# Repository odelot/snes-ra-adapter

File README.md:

# SNES RA Adapter Project

Repository of the **SNES RetroAchievements Adapter**, a maker project that brings Internet connectivity and achievements to the original Super Nintendo, using a real console and a real cartridge, with no PC and no emulator. It is the big brother of the [NES RA Adapter](https://github.com/odelot/nes-ra-adapter), and it is powered by the amazing [RetroAchievements](https://retroachievements.org) community.

<!-- TODO: replace with the YouTube link when the video is out -->
**Video:** *coming soon*

---

## Table of Contents

- [Disclaimer](#disclaimer)
- [Introduction](#introduction)
- [Getting Started (How to Build)](#getting-started--how-to-build)
- [Architecture and Functionality](#architecture-and-functionality)
- [Compatibility](#compatibility)
- [Limitations](#limitations)
- [General Information](#general-information)
- [Version History](#version-history)
- [Roadmap](#roadmap)
- [Contributions](#contributions)
- [License](#license)
- [FAQ](#faq)
- [Acknowledgments](#acknowledgments)
- [Similar Projects](#similar-projects)

---

## Disclaimer

The project is not responsible for any use or damage it may cause. Build and use it at your own risk.

This is a **PROTOTYPE**. It works, but it still needs to evolve into a final version: revised hardware, a case, extensive testing and easy replication. v0.1 has no case, needs a small mod (2 cut traces and 2 wires), and was tested on an opened console. Only build it if you know what you're doing.

---

## Introduction

The **SNES RA Adapter** sits between the cartridge and the console, like a Game Genie. It turns your original Super Nintendo into an Internet-connected machine that unlocks RetroAchievements in real time:

- **Identifies the game** by reading the whole cartridge and computing the same MD5 hash RetroAchievements uses for ROM files. It knows exactly which game, and which version, is in the slot.
- **Monitors the console memory:** it listens to every write to the 128 KB of WRAM (DMA included) and to the cartridge save RAM, and runs rcheevos, the same code emulators use, 60 times per second.
- **Shows your progress:** on its own 1.3" screen, with a buzzer, and on a web page you can open on your phone (`http://snes-ra-adapter.local`). No app needed.

### Repository Organization

- **[hardware](hardware)**: KiCad project and Gerber files of prototype v0.1, the bill of materials, the required mod and the assembly guide.
- **[snes-pico-firmware](snes-pico-firmware)**: firmware for the WeAct Studio RP2350B Core Board. It handles cartridge identification, bus capture and rcheevos.
- **[snes-esp-firmware](snes-esp-firmware)**: firmware for the ESP32-C3 Super Mini. It handles Wi-Fi, the RetroAchievements API, the LCD, the buzzer and the web portal.
- **[misc](misc)**: auxiliary files: the `TFT_eSPI` configuration for the LCD.

---

## Getting Started / How to Build

### 1. Acquire the parts

All parts are through-hole: a 74HC4066 bus switch bank, a WeAct RP2350B board, an ESP32-C3 Super Mini, a 1.3" ST7789 LCD, a SNES 62-pin cartridge slot and a few passives. The full list is in the **[hardware bill of materials](hardware/README.md#bill-of-materials)**.

### 2. Order the PCB

Upload [`hardware/proto-v0.1/fab/snes-ra-proto-v0.1.zip`](hardware/proto-v0.1/fab/snes-ra-proto-v0.1.zip) to a pcb fab:

- 2 layers, **1.2 mm** thick (like an original cartridge).
- ENIG finish.
- Gold fingers with a 45° bevel.

### 3. Do the mod and assemble the board

Prototype v0.1 has A22 and /RD swapped on the Pico. **Every board needs 2 cut traces and 2 wires**, which are easier before the WeAct is soldered. The step by step, with pictures, and the assembly order are in the **[hardware README](hardware/README.md#required-mod-2-cuts--2-wires)**.

### 4. Flash the firmware

Flash both modules over USB **before** plugging the board into the console.

1. **Raspberry Pi Pico (WeAct RP2350B):**
   - Hold the **BOOT** button and connect the board over USB.
   - Copy `snes-pico-firmware.uf2` to the `RP2350` drive that shows up.
   - To build the `.uf2` yourself, see [snes-pico-firmware](snes-pico-firmware/README.md#building).
2. **ESP32-C3 Super Mini:**
   - Compile and upload with the Arduino IDE.
   - Then upload the `data` folder (web portal) to LittleFS.
   - Before compiling, copy [`misc/TFT_eSPI/User_Setup.h`](misc/TFT_eSPI/User_Setup.h) into your `TFT_eSPI` library folder.
   - The step by step is in [snes-esp-firmware](snes-esp-firmware/README.md).

### 5. First use

1. With the console **off**, plug the adapter into the cartridge slot and the game into the adapter.
2. Turn the console on. On the first boot, the screen asks you to configure the adapter:
   - With your phone, connect to the Wi-Fi network **`SNES_RA_ADAPTER`** (password `12345678`).
   - Open `http://192.168.1.1`.
   - Enter your Wi-Fi network and your RetroAchievements username and password.
3. The adapter connects, logs in, reads the cartridge and starts the game. Have fun!
4. To follow your progress on the phone, open `http://snes-ra-adapter.local` (the phone must be on the same Wi-Fi network).

To erase the configuration, hold the button (SW1) for 5 seconds while the adapter starts.

---

## Architecture and Functionality

```mermaid
flowchart LR
    SNES[SNES console] <-- cartridge bus --> SW[74HC4066 bus switches]
    SW <--> CART[Game cartridge]
    SW -. listen .-> PICO[RP2350B<br/>cart ID + bus capture + rcheevos]
    PICO <-- UART --> ESP[ESP32-C3<br/>Wi-Fi + LCD + buzzer + web portal]
    ESP <-- HTTPS --> RA[(RetroAchievements)]
```

### Raspberry Pi Pico (WeAct RP2350B, 48 GPIO)

- **Game identification:**
  - At power-on it holds the console in reset and isolates it from the cartridge with the bus switches.
  - It reads the whole ROM and computes its MD5. It also handles ROMs whose size is not a power of two, which show up mirrored on the bus.
  - Then it releases the console.
- **Memory monitoring (core 1):**
  - PIO state machines capture **one sample per write cycle** on the bus: WRAM writes, cartridge SRAM writes and the B-bus WRAM port ($2180–$2183), which games use to DMA data into WRAM.
  - The two PIOs of the RP2350B share an overlapping GPIO window, so no pin is duplicated.
  - Core 1 keeps a full copy of the 128 KB WRAM and of the cartridge SRAM.
- **Achievements (core 0):**
  - rcheevos runs on every **real vblank**, detected from the OAM DMA burst the game fires in the NMI handler, with a timer as fallback.
  - Each frame is evaluated on an atomic snapshot of the memory.
  - Pressing RESET on the console resets the rcheevos runtime state, just like an emulator.

More details in [snes-pico-firmware](snes-pico-firmware/README.md).

### ESP32

- **Connectivity and interface:** gives the SNES Internet access, talks to the RetroAchievements API, and shows the achievements on the LCD with sound effects on the buzzer.
- **Configuration:** Wi-Fi and RetroAchievements credentials are stored in EEPROM and set from a smartphone, through the ESP32 access point.
- **Web portal:** a dashboard on your local network (`http://snes-ra-adapter.local`). It shows:
  - the game, rich presence and progress;
  - the full achievement list with filters;
  - live unlock, challenge and progress notifications;
  - an LCD theme picker.

  The Pico is the single source of truth: the ESP32 only relays the data.

---

## Limitations

- **SA-1 games:** the SA-1 is a second processor inside the cartridge, about three times faster than the SNES CPU. It runs the game from its own memory, and most of that data never reaches the cartridge connector, so the adapter can't see it. This is a hardware limit.
- **Large cartridge save RAM:** only LoROM SRAM up to 32 KB and HiROM SRAM up to 8 KB are tracked. Achievements that read the save RAM of carts with more SRAM (Star Ocean, Tales of Phantasia, Dragon Quest VI) won't work yet. Achievements based on the console RAM are not affected.
- **Casual mode:** the prototype runs in casual mode.
- **Flash carts** (SD2SNES / FXPAK, EverDrive): not supported. The adapter needs to read the cartridge to identify the game, and with a flash cart it reads the flash cart's menu instead. To use RetroAchievements with an FXPAK, see [RA2Snes](#similar-projects).
- **Console shell:** v0.1 is a bare board, tested on an opened console. A case and a board that fits a SNES with its shell are on the [roadmap](#roadmap).
- **PAL consoles:** the firmware supports 50 Hz, but it has not been tested on a PAL console yet.

---

## General Information

- **Power:** the adapter is powered by the console's +5 V (cartridge connector). A Schottky diode keeps the USB of the modules from powering the console.
- **Logic level conversion (5 V vs 3.3 V):** there is no level shifter.
  - The RP2350 inputs are 5 V tolerant, so the Pico listens to the bus directly.
  - The Pico only drives the cartridge (at 3.3 V, which the ROMs read as HIGH) during identification, while the console is isolated by the bus switches and held in reset.

---

## Version History

- **Prototype v0.1 (2026-11):** first PCB. Everything is through-hole, with a 74HC4066 bus switch bank. Adds automatic cartridge identification (ROM MD5), cartridge SRAM capture, the B-bus WRAM port, vblank-paced frames, console reset detection and a web portal with LCD themes.

- **"Spaghetti edition" (2026-06):** WeAct RP2350B (48 GPIO) with almost 50 wires soldered straight to the console motherboard. It validated the whole bus capture by beating Star Fox, Mega Man X and EarthBound. The game was still picked from a list.
- **Proof of concept (2025-04):** reused the NES adapter with the original Pico. It could not see the whole memory range or identify games, but it caught memory writes and unlocked a few achievements.

---

## Roadmap

- **v0.1b:**
  - A22 and /RD fixed in copper (no mod).
  - ESP32-S3-Zero, for more RAM for large achievement sets.
  - A 3D-printed case in the style of the Super Game Boy, so it fits a SNES with its shell.
- **Slim version:** SN74CBT3245 bus switches, 4-layer board, about the size of a cartridge.
- **Firmware:** large SRAM carts (A17–A23 capture), ExHiROM, hardcore mode and leaderboards.

---

## Contributions

Everyone is welcome to contribute!

- Submit improvements and pull requests via GitHub.
- Join our Discord channel: [https://discord.com/invite/6eYGq7NNfF](https://discord.com/invite/6eYGq7NNfF)
- Support us on [Patreon](https://www.patreon.com/RetroAchievementsHardwareLab) or by [buying a coffee](https://buymeacoffee.com/nes.ra.adapter).

---

## License

- The source code is distributed under the **GPLv3** license.
- The PCB design files are distributed under the **CC-BY-4.0** license.

---

## FAQ

- **Q: Are you planning to sell the adapter?**
- **A:** No. This is a fully open-source, community-driven DIY project.
<br/>

- **Q: So how can I get one?**
- **A:** It's a DIY project: you can build it yourself! Every part is through-hole, so it is a good soldering project. As with other open-source projects, the community may step in to build units for people who don't want to build their own.
<br/>

- **Q: Do I need to modify my SNES?**
- **A:** No. The adapter plugs into the cartridge slot. The prototype v0.1 is a bare board, though, and was tested on an opened console. The next revision fits a SNES with its shell.
<br/>

- **Q: Do I need to connect it to a computer?**
- **A:** No! It has built-in Wi-Fi and all achievement processing happens on the adapter. You configure it from your phone.
<br/>

- **Q: Will it work with Super Famicom?**
- **A:** The cartridge connector is the same, but it has not been tested yet.
<br/>

- **Q: Why doesn't Super Mario RPG work?**
- **A:** It uses the SA-1 chip, which keeps the game data inside the cartridge, where the adapter can't see it. See [Limitations](#limitations).
<br/>

---

## Acknowledgments

- Thanks to **RetroAchievements** and its community for providing achievements for nearly all games, and for always supporting, testing and sharing.
- Thanks to the **Patreon supporters**, who covered part of the cost of these prototypes.

## Similar Projects

- **RA2Snes**: [https://github.com/Factor-64/RA2Snes](https://github.com/Factor-64/RA2Snes). A program built with Qt and C++ that bridges the QUsb2Snes web server and the rcheevos client, so you can unlock achievements on real Super Nintendo hardware through the SD2Snes USB port.
- **NES RA Adapter**: [https://github.com/odelot/nes-ra-adapter](https://github.com/odelot/nes-ra-adapter). The same idea for the NES and the Famicom.

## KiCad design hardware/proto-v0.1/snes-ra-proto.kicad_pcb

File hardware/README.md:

# SNES RA Adapter: hardware

The adapter is a single board that works like a Game Genie. Its bottom edge plugs into the console's cartridge slot, and the game cartridge plugs into a female slot on its top edge. The screen sits on the front.

```
hardware/
  proto-v0.1/        KiCad 9 project of prototype v0.1, exactly as fabricated and tested
    fab/             Gerber + drill zip, ready to upload to a pcb fab
  lib/               custom symbols and footprints used by the project (snes-ra-adapter)
  docs/
    netlist.md       full connection table (edge pin -> switch -> Pico GPIO, ESP32, power)
    v0.1-mod/        images of the 2 cuts + 2 wires every v0.1 board needs
```

---

## Prototype v0.1

- **Board:** 120 × 110 mm, 2 layers, 1.2 mm thick (the same as an original cartridge). Every part is through-hole, so it is beginner-friendly to solder.
- **Bus isolation:** 9× 74HC4066 (DIP-14) on 35 lines: A0–A23, D0–D7, /RD, /WR and /CART. While the adapter reads the cartridge, the switches open and the console is held in reset. During gameplay they stay closed and the Pico only listens.
- **Microcontrollers:** WeAct Studio RP2350B Core Board (48 GPIO) and ESP32-C3 Super Mini, both soldered as modules.
- **Screen:** 1.3" 240×240 ST7789 LCD (7-pin) in a 1x7 female header.
- **Bottom strip (30 mm):** this is the part that goes into the console. It is 89 mm wide and has no components.
- **Pico USB-C:** points down, through a corridor with no components, so the cable still fits with the board in the console.
- **Back face:**
  - The ESP32-C3 sits behind the LCD, with its USB on the left edge. There is no copper plane under its antenna.
  - The buzzer (BZ1), its driver transistor (Q2) and R4 are next to it.
- **Tested on an opened console.** v0.1 has no case and was not designed around the SNES shell or the power-switch lock. The case and the shell fit come in the next revision (v0.1b).

The complete connection table is in [docs/netlist.md](docs/netlist.md).

### Bill of materials

| Qty | Part | Refs |
|---:|---|---|
| 1 | PCB (see [Ordering the PCB](#ordering-the-pcb)) | |
| 1 | SNES 62-pin cartridge slot, 2.5 mm pitch | J2 |
| 9 | 74HC4066 DIP-14 (sockets optional) | U1–U9 |
| 1 | WeAct Studio RP2350B Core Board + 2× female headers | U10 |
| 1 | ESP32-C3 Super Mini (the PLUS version with an external antenna works better) + female headers | U11 |
| 1 | LCD 1.3" 240×240 ST7789, 7 pins + 1x7 female header | J3 |
| 9 | 100 nF ceramic capacitor (5 mm pitch) | C1–C9 |
| 1 | 47 µF 16 V electrolytic capacitor | C10 |
| 1 | 10 µF 10 V (or higher) electrolytic capacitor | C11 |
| 1 | 1N5817 Schottky diode | D1 |
| 2 | BC548 NPN transistor | Q1, Q2 |
| 3 | 10 kΩ resistor | R1, R3, R5 |
| 2 | 1 kΩ resistor | R2, R4 |
| 1 | Passive buzzer, 12 mm | BZ1 |
| 1 | 6×6 mm tactile push button | SW1 |
| 1 | Bi-color LED 3 mm, green/red, common cathode (*optional*) | D2 |
| 2 | 100 Ω resistor (*optional*, only with D2) | R6, R7 |
| 1 | 1x3 pin header (*optional*, UART debug) | J4 |
| 2 | Short pieces of thin insulated wire (for the [mod](#required-mod-2-cuts--2-wires)) | |

Notes:

- **Resistors:** mounted standing up (2.54 mm pitch).
- **JP1:** a solder jumper that comes bridged 1-2 from the factory (pull-down, so the bus starts isolated at power-on). Leave it as is.
- **BZ1:** the footprint has 5.0 mm between the legs (TDK PS1240). The common 12 mm passive buzzers have 6.5 mm, so bend the legs inwards to fit.
- **C10 and C11:** the footprints are for Ø6.3 mm / 2.5 mm and Ø5 mm / 2.0 mm parts. Smaller capacitors (Ø4 mm, 1.5 mm pitch) also fit, just open the legs a little.
- **J4:** an optional UART debug header (1 GND, 2 Pico TX, 3 Pico RX).

### Ordering the PCB

Upload [`proto-v0.1/fab/snes-ra-proto-v0.1.zip`](proto-v0.1/fab/snes-ra-proto-v0.1.zip) to a pcb fab. These are the settings used for the tested boards:

- 2 layers, **1.2 mm** thick.
- ENIG surface finish.
- **Gold fingers: yes**, with a **45° bevel** on the edge connector.

### Required mod (2 cuts + 2 wires)

Prototype v0.1 has two Pico pins swapped. A22 goes to GP37 and /RD goes to GP29, but the firmware needs **A22 on GP29**. That is because GP29 is inside the PIO0 capture window, and A22 tells a WRAM mirror access from a direct $7E/$7F access. **Every v0.1 board needs this mod.** It is already fixed in copper in the next revision.

The marks below are on the WeAct (U10) footprint, on the PCB itself. The cuts are easiest **before** soldering the WeAct headers. Use a hobby knife, and scrape until the copper is gone.

1. **Cut 1 (front, screen side):** cut the trace that leaves the **GP29** pad, right next to the pad.

2. **Cut 2 (back, solder side):** cut the trace that leaves the **GP37** pad, right next to the pad.
3. **Wire 1:** solder a wire from **GP29** to **U6 pin 3** (A22).
4. **Wire 2:** solder a wire from **GP37** to **U9 pin 3** (/RD).

5. **Check with a multimeter:**
   - GP29 must have continuity with U6 pin 3, and **not** with U9 pin 3.
   - GP37 must have continuity with U9 pin 3, and **not** with U6 pin 3.

The Pico firmware expects the mod by default (`#define A22_ON_GP29` in `snes-pico-firmware/src/main.c`).

### Assembly order

1. **Mod:** make the [2 cuts](#required-mod-2-cuts--2-wires).
2. **Low parts first:** resistors, diode, ceramic capacitors and the 74HC4066 (or their sockets). Watch the orientation of U1–U9.
3. **Back parts:** ESP32-C3 headers, BZ1, Q2 and R4. Their pins come out on the front, under the LCD, so solder them **before** the LCD header.
4. **Front parts:** Q1, electrolytic capacitors, SW1, the optional D2 and the WeAct headers.
5. **LCD header and cartridge slot (J2).**
6. **Mod wires:** solder the 2 wires on the back.
7. **Before the first power-up:**
   - Check that there is no short between +5V and GND.
   - Flash both firmwares over USB, **with the board out of the console**.
   - Then plug the modules in.

### Status

- **v0.1:** fabricated (Oct 2026) and tested with the mod above.
- **Games beaten / tested:** Super Mario World, Super Metroid, Star Fox and Yoshi's Island (see the main [README](../README.md)).
- **KiCad files:** ERC has 0 violations. DRC shows 0 violations, 0 unconnected items and 0 schematic parity issues. The files are the ones that went to fab, so they still have the swap the mod fixes.

---

## What's next

- **v0.1b:** v0.1 with A22 and /RD fixed in copper, ESP32-S3-Zero instead of the C3 (more RAM for large achievement sets) and parts placed for a 3D-printed case in the style of the Super Game Boy, so it fits a SNES with its shell.
- **Slim version:** SN74CBT3245 bus switches instead of the 4066s, 4 layers, about the size of a cartridge board.

These boards are still being validated and will be published once they are tested.

## License

The PCB design files are distributed under the **CC-BY-4.0** license.

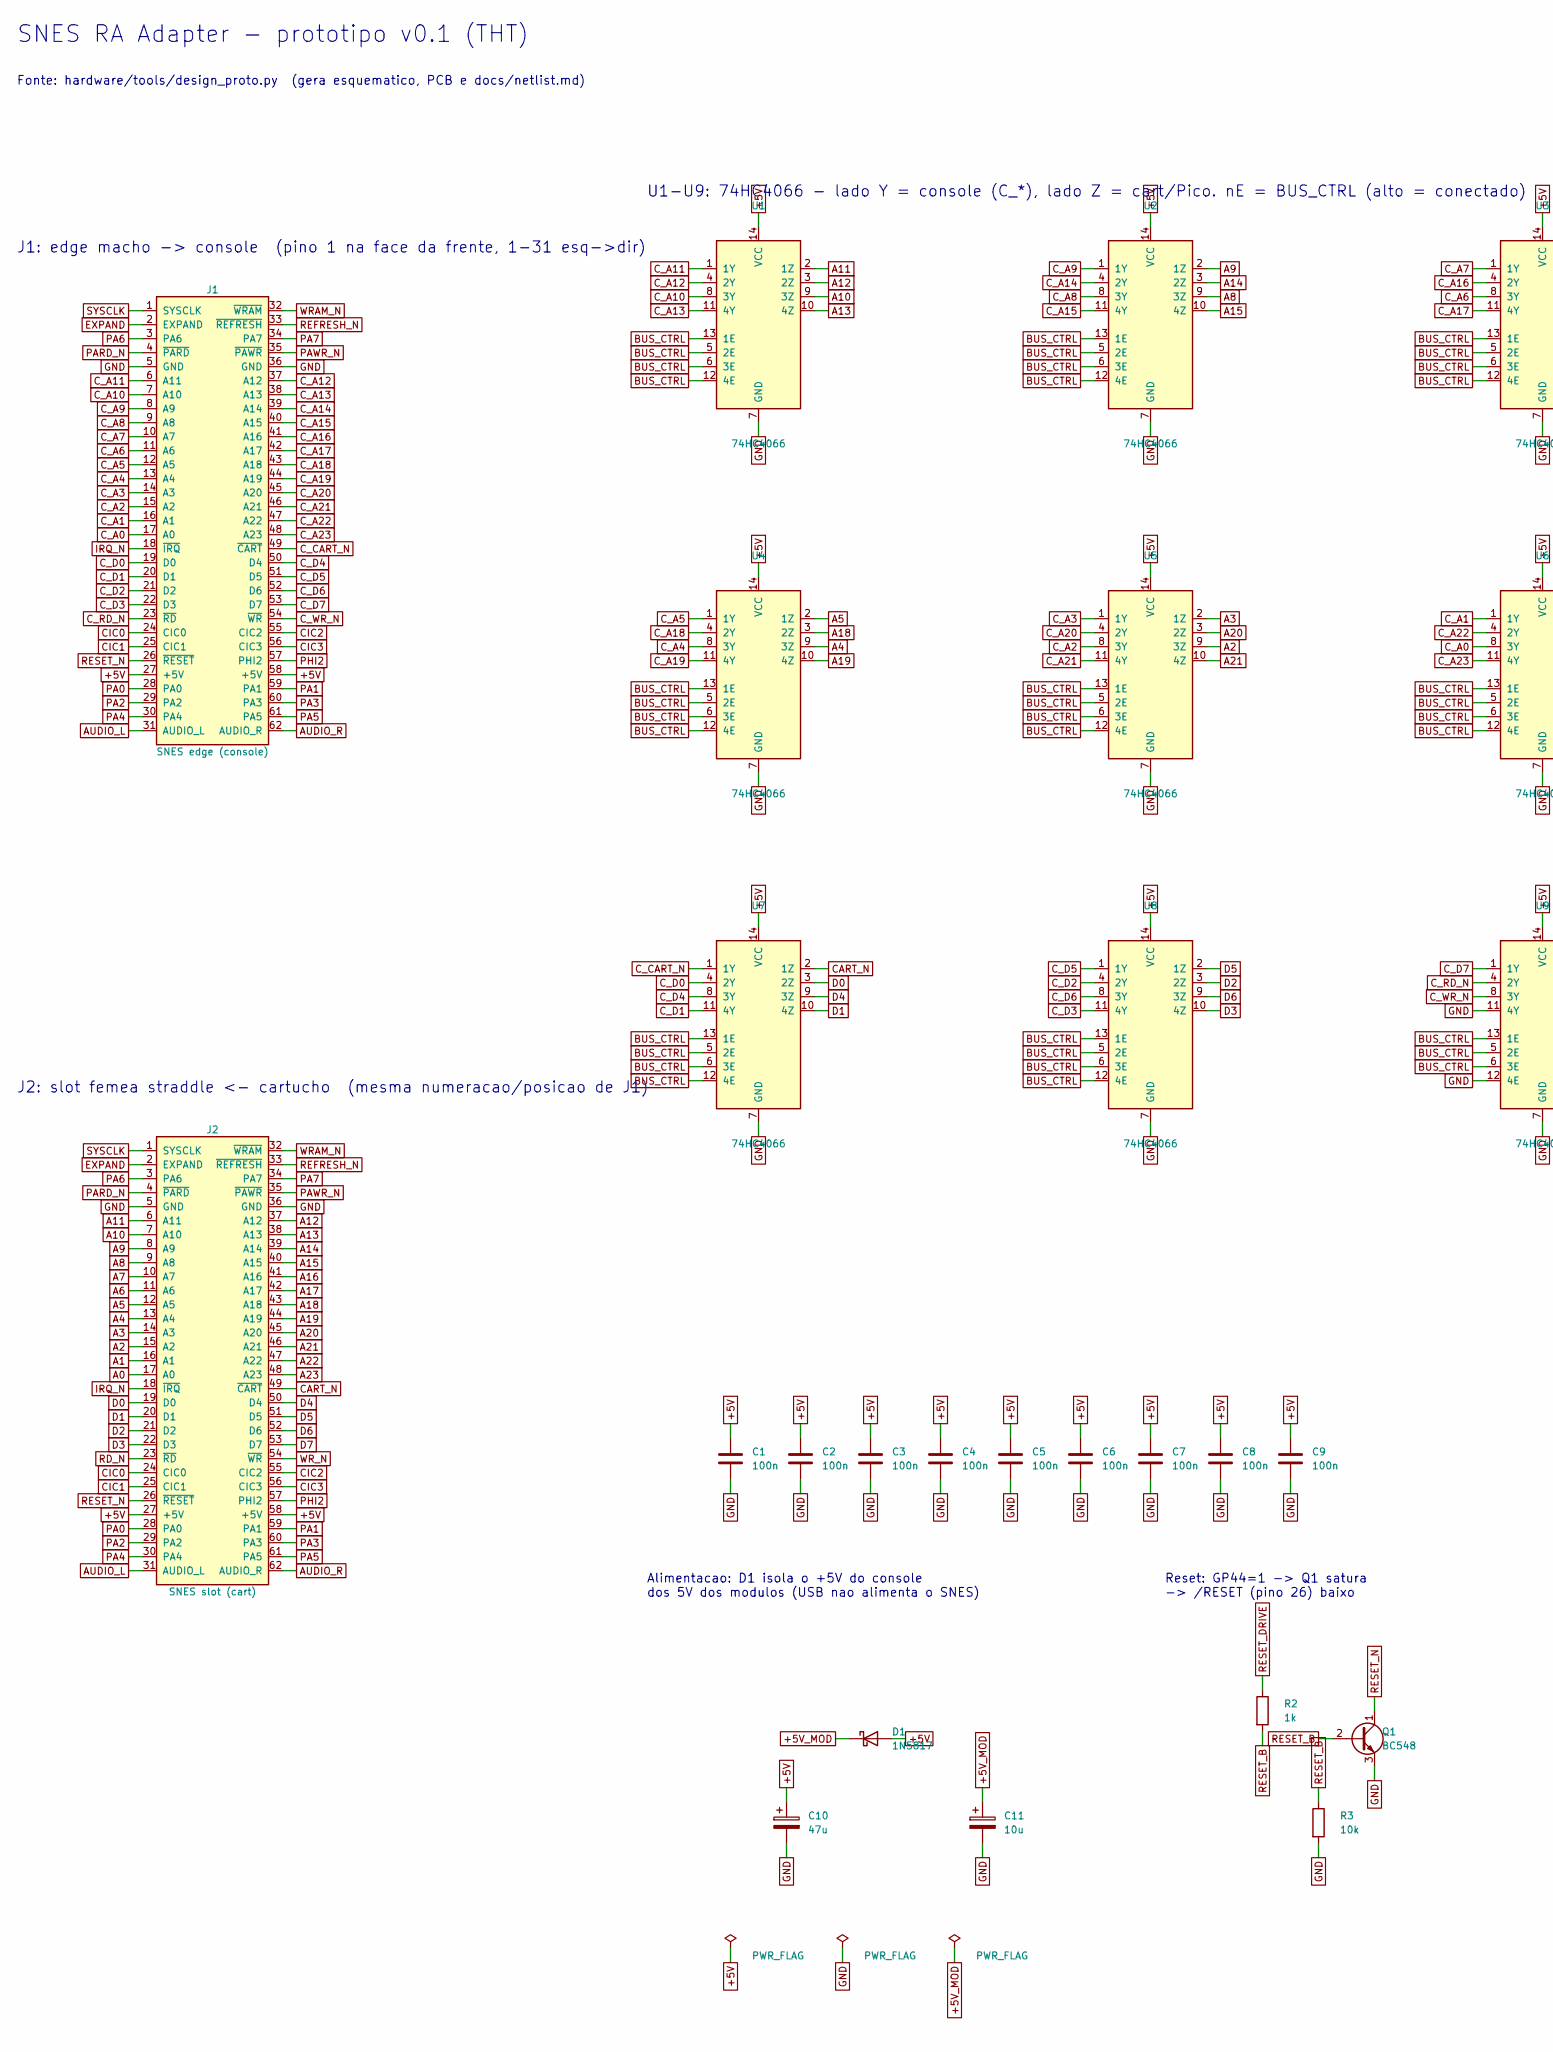
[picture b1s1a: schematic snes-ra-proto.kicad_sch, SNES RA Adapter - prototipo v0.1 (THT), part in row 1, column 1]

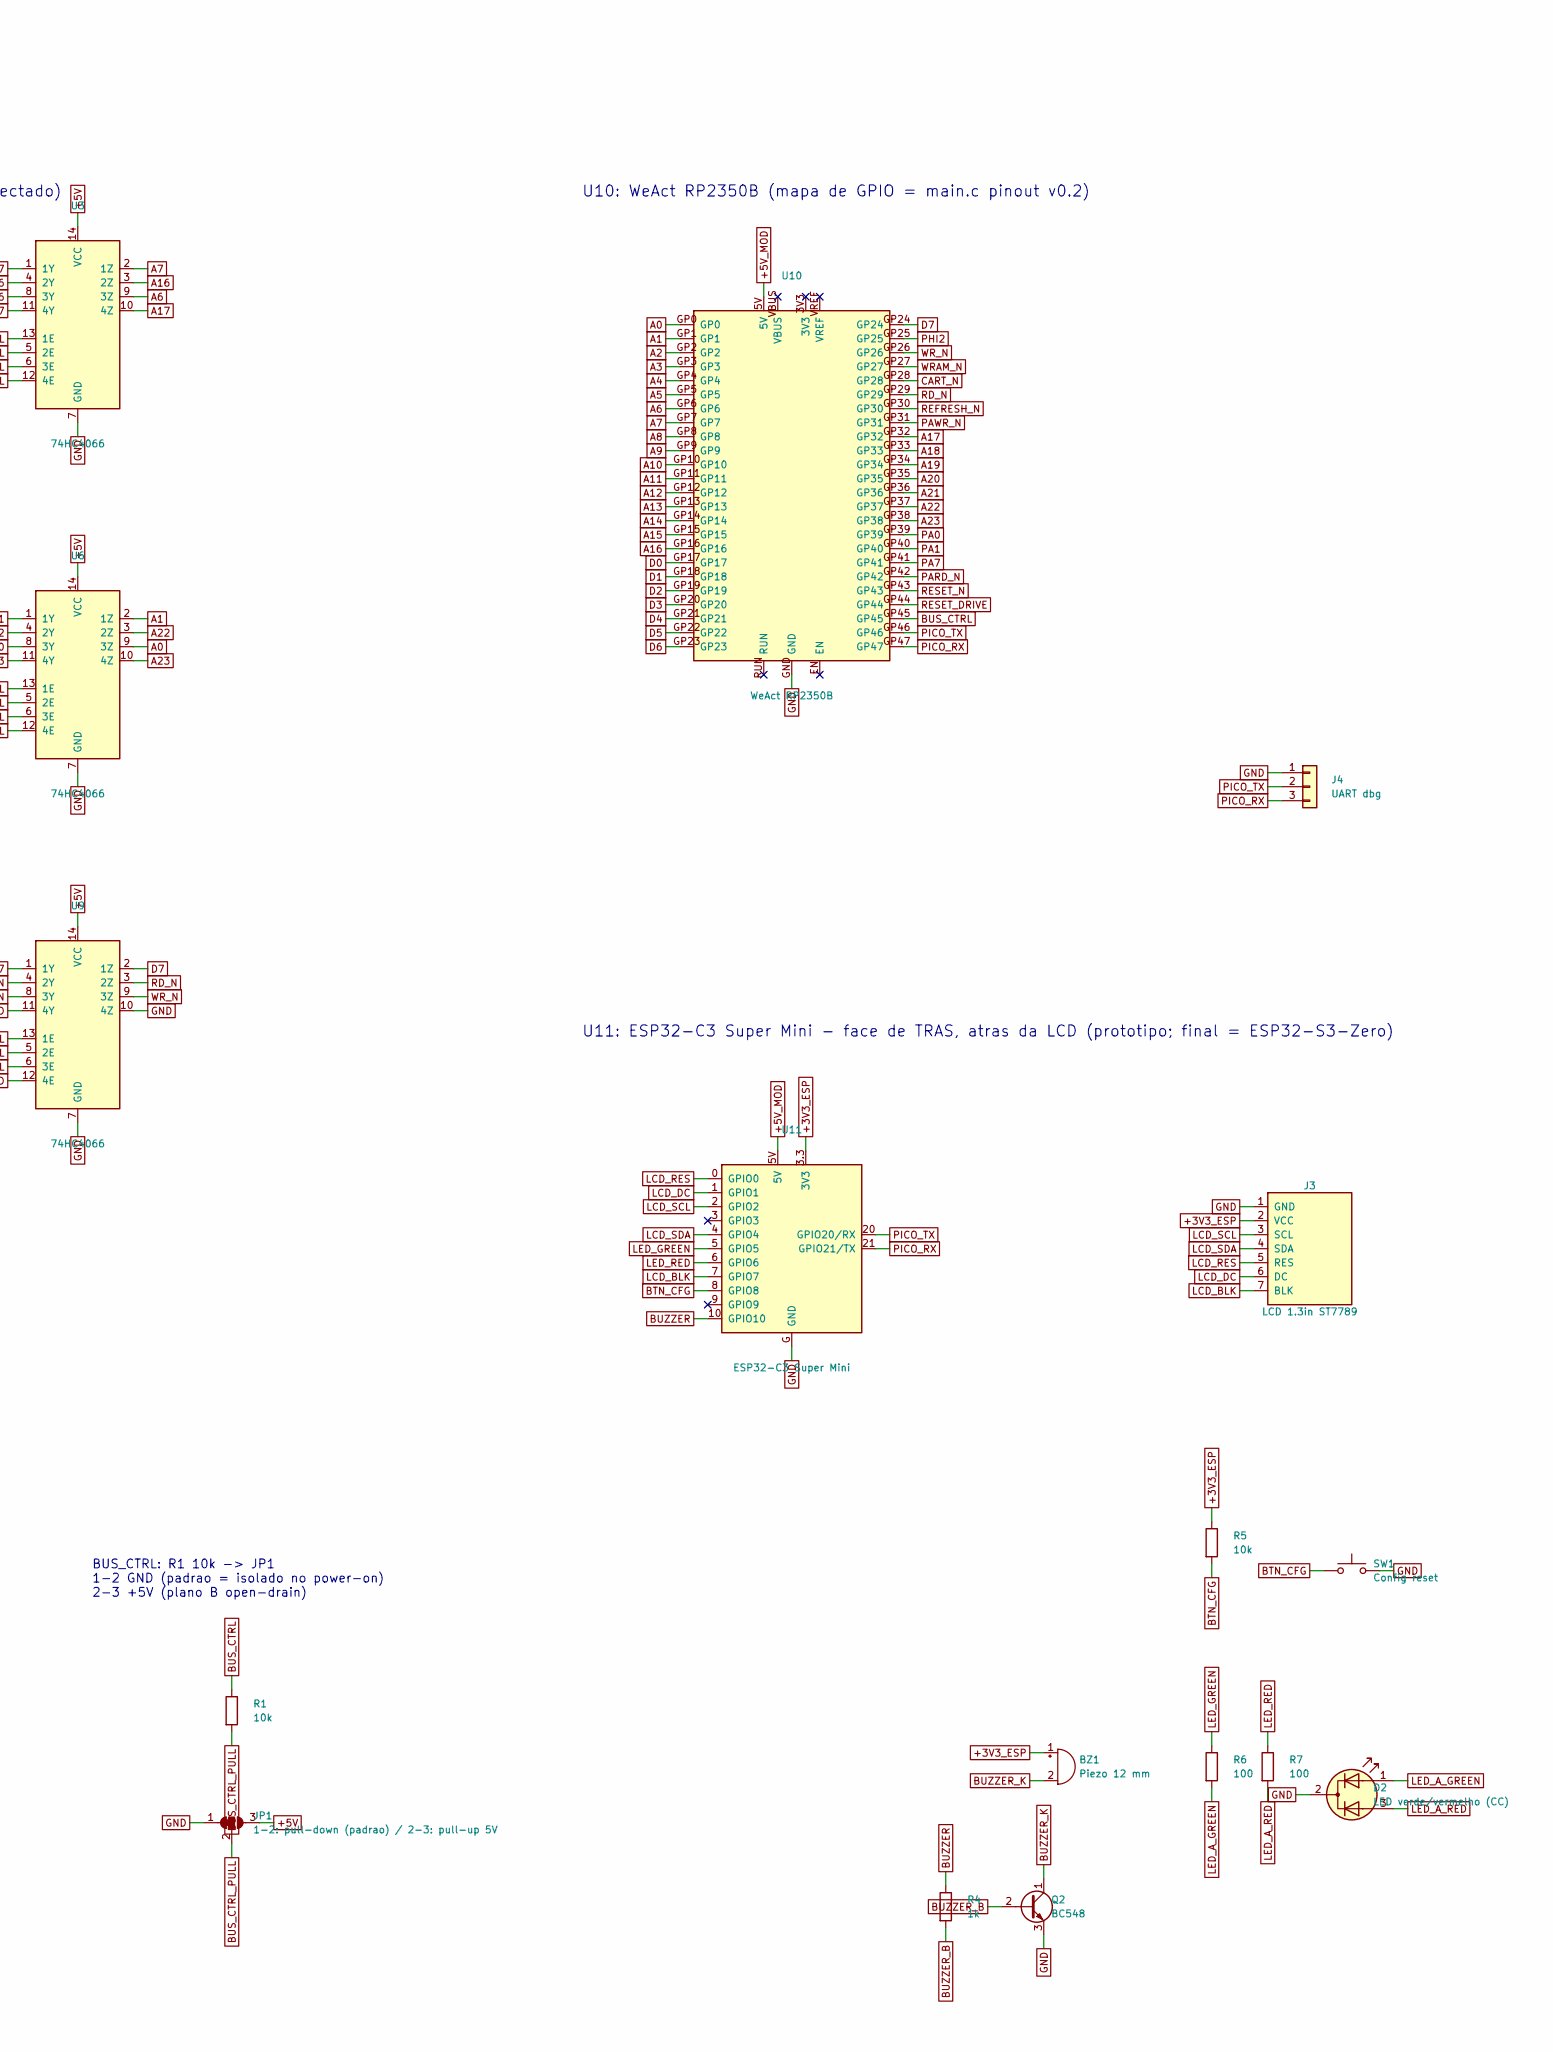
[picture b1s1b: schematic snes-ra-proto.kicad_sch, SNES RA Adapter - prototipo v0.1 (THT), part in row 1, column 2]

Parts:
BZ1: Piezo 12 mm; Buzzer_TDK_PS1240P02BT_D12.2mm_H6.5mm
C1, C2, C3, C4, C5, C6, C7, C8, C9: 100n; C_Disc_D5.0mm_W2.5mm_P5.00mm
C10: 47u; CP_Radial_D6.3mm_P2.50mm
C11: 10u; CP_Radial_D5.0mm_P2.00mm
D1: 1N5817; D_DO-41_SOD81_P10.16mm_Horizontal
D2: LED verde/vermelho (CC); LED_D3.0mm-3
J1: SNES edge (console); SNES_CartEdge_62
J2: SNES slot (cart); SNES_Slot_62_Straddle
J3: LCD 1.3in ST7789; LCD_ST7789_1.3in_7pin
J4: UART dbg; PinHeader_1x03_P2.54mm_Vertical
JP1: 1-2: pull-down (padrao) / 2-3: pull-up 5V; SolderJumper-3_P1.3mm_Bridged12_RoundedPad1.0x1.5mm
Q1, Q2: BC548; TO-92_Inline
R1, R3, R5: 10k; R_Axial_DIN0207_L6.3mm_D2.5mm_P2.54mm_Vertical
R2, R4: 1k; R_Axial_DIN0207_L6.3mm_D2.5mm_P2.54mm_Vertical
R6, R7: 100; R_Axial_DIN0207_L6.3mm_D2.5mm_P2.54mm_Vertical
SW1: Config reset; SW_PUSH_6mm
U1, U2, U3, U4, U5, U6, U7, U8, U9: 74HC4066; DIP-14_W7.62mm
U10: WeAct RP2350B; WeAct_RP2350B_CoreBoard
U11: ESP32-C3 Super Mini; ESP32-C3_SuperMini

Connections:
+3V3_ESP: BZ1.1 (+), J3.2 (VCC), R5.1, U11.3.3 (3V3)
+5V: C1.1, C2.1, C3.1, C4.1, C5.1, C6.1, C7.1, C8.1, C9.1, C10.1, D1.2 (A), J1.27 (+5V), J1.58 (+5V), J2.27 (+5V), J2.58 (+5V), JP1.3 (B), U1.14 (VCC), U2.14 (VCC), U3.14 (VCC), U4.14 (VCC), U5.14 (VCC), U6.14 (VCC), U7.14 (VCC), U8.14 (VCC), U9.14 (VCC)
+5V_MOD: C11.1, D1.1 (K), U10.5V, U11.5V
A0: J2.17 (A0), U6.9 (3Z), U10.GP0
A1: J2.16 (A1), U6.2 (1Z), U10.GP1
A2: J2.15 (A2), U5.9 (3Z), U10.GP2
A3: J2.14 (A3), U5.2 (1Z), U10.GP3
A4: J2.13 (A4), U4.9 (3Z), U10.GP4
A5: J2.12 (A5), U4.2 (1Z), U10.GP5
A6: J2.11 (A6), U3.9 (3Z), U10.GP6
A7: J2.10 (A7), U3.2 (1Z), U10.GP7
A8: J2.9 (A8), U2.9 (3Z), U10.GP8
A9: J2.8 (A9), U2.2 (1Z), U10.GP9
A10: J2.7 (A10), U1.9 (3Z), U10.GP10
A11: J2.6 (A11), U1.2 (1Z), U10.GP11
A12: J2.37 (A12), U1.3 (2Z), U10.GP12
A13: J2.38 (A13), U1.10 (4Z), U10.GP13
A14: J2.39 (A14), U2.3 (2Z), U10.GP14
A15: J2.40 (A15), U2.10 (4Z), U10.GP15
A16: J2.41 (A16), U3.3 (2Z), U10.GP16
A17: J2.42 (A17), U3.10 (4Z), U10.GP32
A18: J2.43 (A18), U4.3 (2Z), U10.GP33
A19: J2.44 (A19), U4.10 (4Z), U10.GP34
A20: J2.45 (A20), U5.3 (2Z), U10.GP35
A21: J2.46 (A21), U5.10 (4Z), U10.GP36
A22: J2.47 (A22), U6.3 (2Z), U10.GP37
A23: J2.48 (A23), U6.10 (4Z), U10.GP38
AUDIO_L: J1.31 (AUDIO_L), J2.31 (AUDIO_L)
AUDIO_R: J1.62 (AUDIO_R), J2.62 (AUDIO_R)
BTN_CFG: R5.2, SW1.1, U11.8 (GPIO8)
BUS_CTRL: R1.1, U1.5 (2E), U1.6 (3E), U1.12 (4E), U1.13 (1E), U2.5 (2E), U2.6 (3E), U2.12 (4E), U2.13 (1E), U3.5 (2E), U3.6 (3E), U3.12 (4E), U3.13 (1E), U4.5 (2E), U4.6 (3E), U4.12 (4E), U4.13 (1E), U5.5 (2E), U5.6 (3E), U5.12 (4E), U5.13 (1E), U6.5 (2E), U6.6 (3E), U6.12 (4E), U6.13 (1E), U7.5 (2E), U7.6 (3E), U7.12 (4E), U7.13 (1E), U8.5 (2E), U8.6 (3E), U8.12 (4E), U8.13 (1E), U9.5 (2E), U9.6 (3E), U9.13 (1E), U10.GP45
BUS_CTRL_PULL: JP1.2 (C), R1.2
BUZZER: R4.1, U11.10 (GPIO10)
BUZZER_B: Q2.2 (B), R4.2
BUZZER_K: BZ1.2 (-), Q2.1 (C)
CART_N: J2.49 (~CART), U7.2 (1Z), U10.GP28
CIC0: J1.24 (CIC0), J2.24 (CIC0)
CIC1: J1.25 (CIC1), J2.25 (CIC1)
CIC2: J1.55 (CIC2), J2.55 (CIC2)
CIC3: J1.56 (CIC3), J2.56 (CIC3)
C_A0: J1.17 (A0), U6.8 (3Y)
C_A1: J1.16 (A1), U6.1 (1Y)
C_A2: J1.15 (A2), U5.8 (3Y)
C_A3: J1.14 (A3), U5.1 (1Y)
C_A4: J1.13 (A4), U4.8 (3Y)
C_A5: J1.12 (A5), U4.1 (1Y)
C_A6: J1.11 (A6), U3.8 (3Y)
C_A7: J1.10 (A7), U3.1 (1Y)
C_A8: J1.9 (A8), U2.8 (3Y)
C_A9: J1.8 (A9), U2.1 (1Y)
C_A10: J1.7 (A10), U1.8 (3Y)
C_A11: J1.6 (A11), U1.1 (1Y)
C_A12: J1.37 (A12), U1.4 (2Y)
C_A13: J1.38 (A13), U1.11 (4Y)
C_A14: J1.39 (A14), U2.4 (2Y)
C_A15: J1.40 (A15), U2.11 (4Y)
C_A16: J1.41 (A16), U3.4 (2Y)
C_A17: J1.42 (A17), U3.11 (4Y)
C_A18: J1.43 (A18), U4.4 (2Y)
C_A19: J1.44 (A19), U4.11 (4Y)
C_A20: J1.45 (A20), U5.4 (2Y)
C_A21: J1.46 (A21), U5.11 (4Y)
C_A22: J1.47 (A22), U6.4 (2Y)
C_A23: J1.48 (A23), U6.11 (4Y)
C_CART_N: J1.49 (~CART), U7.1 (1Y)
C_D0: J1.19 (D0), U7.4 (2Y)
C_D1: J1.20 (D1), U7.11 (4Y)
C_D2: J1.21 (D2), U8.4 (2Y)
C_D3: J1.22 (D3), U8.11 (4Y)
C_D4: J1.50 (D4), U7.8 (3Y)
C_D5: J1.51 (D5), U8.1 (1Y)
C_D6: J1.52 (D6), U8.8 (3Y)
C_D7: J1.53 (D7), U9.1 (1Y)
C_RD_N: J1.23 (~RD), U9.4 (2Y)
C_WR_N: J1.54 (~WR), U9.8 (3Y)
D0: J2.19 (D0), U7.3 (2Z), U10.GP17
D1: J2.20 (D1), U7.10 (4Z), U10.GP18
D2: J2.21 (D2), U8.3 (2Z), U10.GP19
D3: J2.22 (D3), U8.10 (4Z), U10.GP20
D4: J2.50 (D4), U7.9 (3Z), U10.GP21
D5: J2.51 (D5), U8.2 (1Z), U10.GP22
D6: J2.52 (D6), U8.9 (3Z), U10.GP23
D7: J2.53 (D7), U9.2 (1Z), U10.GP24
EXPAND: J1.2 (EXPAND), J2.2 (EXPAND)
GND: C1.2, C2.2, C3.2, C4.2, C5.2, C6.2, C7.2, C8.2, C9.2, C10.2, C11.2, D2.2 (K), J1.5 (GND), J1.36 (GND), J2.5 (GND), J2.36 (GND), J3.1 (GND), J4.1, JP1.1 (A), Q1.3 (E), Q2.3 (E), R3.2, SW1.2, U1.7 (GND), U2.7 (GND), U3.7 (GND), U4.7 (GND), U5.7 (GND), U6.7 (GND), U7.7 (GND), U8.7 (GND), U9.7 (GND), U9.10 (4Z), U9.11 (4Y), U9.12 (4E), U10.GND, U11.G (GND)
IRQ_N: J1.18 (~IRQ), J2.18 (~IRQ)
LCD_BLK: J3.7 (BLK), U11.7 (GPIO7)
LCD_DC: J3.6 (DC), U11.1 (GPIO1)
LCD_RES: J3.5 (RES), U11.0 (GPIO0)
LCD_SCL: J3.3 (SCL), U11.2 (GPIO2)
LCD_SDA: J3.4 (SDA), U11.4 (GPIO4)
LED_A_GREEN: D2.1 (A1), R6.2
LED_A_RED: D2.3 (A2), R7.2
LED_GREEN: R6.1, U11.5 (GPIO5)
LED_RED: R7.1, U11.6 (GPIO6)
PA0: J1.28 (PA0), J2.28 (PA0), U10.GP39
PA1: J1.59 (PA1), J2.59 (PA1), U10.GP40
PA2: J1.29 (PA2), J2.29 (PA2)
PA3: J1.60 (PA3), J2.60 (PA3)
PA4: J1.30 (PA4), J2.30 (PA4)
PA5: J1.61 (PA5), J2.61 (PA5)
PA6: J1.3 (PA6), J2.3 (PA6)
PA7: J1.34 (PA7), J2.34 (PA7), U10.GP41
PARD_N: J1.4 (~PARD), J2.4 (~PARD), U10.GP42
PAWR_N: J1.35 (~PAWR), J2.35 (~PAWR), U10.GP31
PHI2: J1.57 (PHI2), J2.57 (PHI2), U10.GP25
PICO_RX: J4.3, U10.GP47, U11.21 (GPIO21/TX)
PICO_TX: J4.2, U10.GP46, U11.20 (GPIO20/RX)
RD_N: J2.23 (~RD), U9.3 (2Z), U10.GP29
REFRESH_N: J1.33 (~REFRESH), J2.33 (~REFRESH), U10.GP30
RESET_B: Q1.2 (B), R2.2, R3.1
RESET_DRIVE: R2.1, U10.GP44
RESET_N: J1.26 (~RESET), J2.26 (~RESET), Q1.1 (C), U10.GP43
SYSCLK: J1.1 (SYSCLK), J2.1 (SYSCLK)
WRAM_N: J1.32 (~WRAM), J2.32 (~WRAM), U10.GP27
WR_N: J2.54 (~WR), U9.9 (3Z), U10.GP26

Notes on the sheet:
SNES RA Adapter - prototipo v0.1 (THT)
Fonte: hardware/tools/design_proto.py (gera esquematico, PCB e docs/netlist.md)
J1: edge macho -> console (pino 1 na face da frente, 1-31 esq->dir)
J2: slot femea straddle <- cartucho (mesma numeracao/posicao de J1)
U1-U9: 74HC4066 - lado Y = console (C_*), lado Z = cart/Pico. nE = BUS_CTRL (alto = conectado)
Alimentacao: D1 isola o +5V do console dos 5V dos modulos (USB nao alimenta o SNES)
Reset: GP44=1 -> Q1 satura -> /RESET (pino 26) baixo
BUS_CTRL: R1 10k -> JP1 1-2 GND (padrao = isolado no power-on) 2-3 +5V (plano B open-drain)
U10: WeAct RP2350B (mapa de GPIO = main.c pinout v0.2)
U11: ESP32-C3 Super Mini - face de TRAS, atras da LCD (prototipo; final = ESP32-S3-Zero)

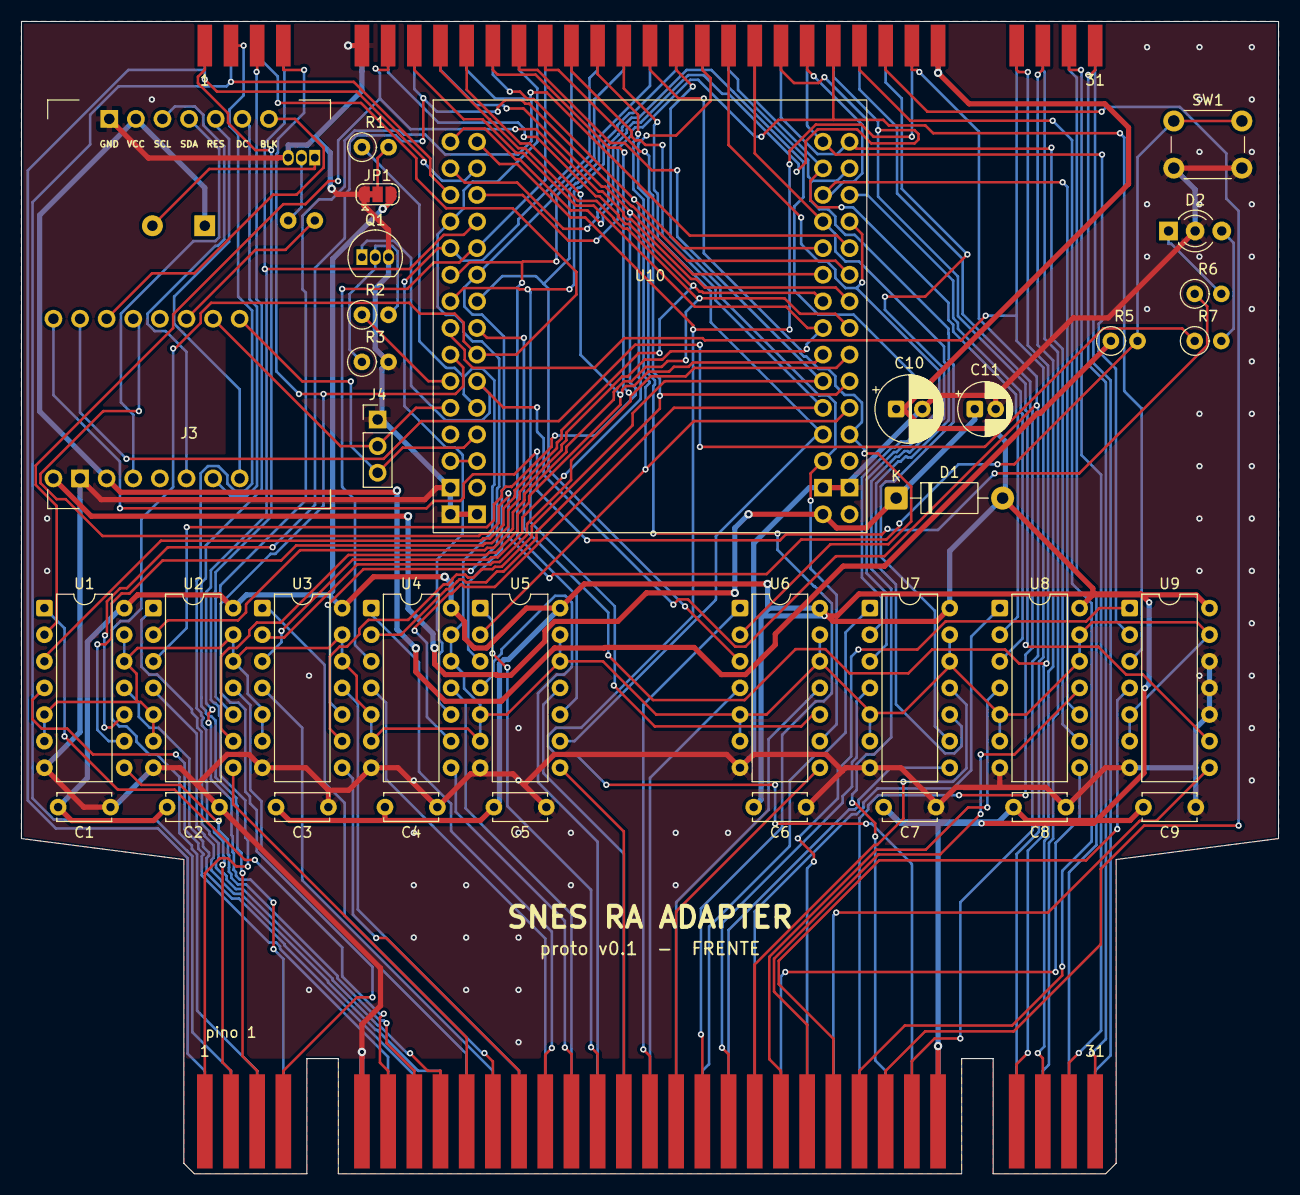
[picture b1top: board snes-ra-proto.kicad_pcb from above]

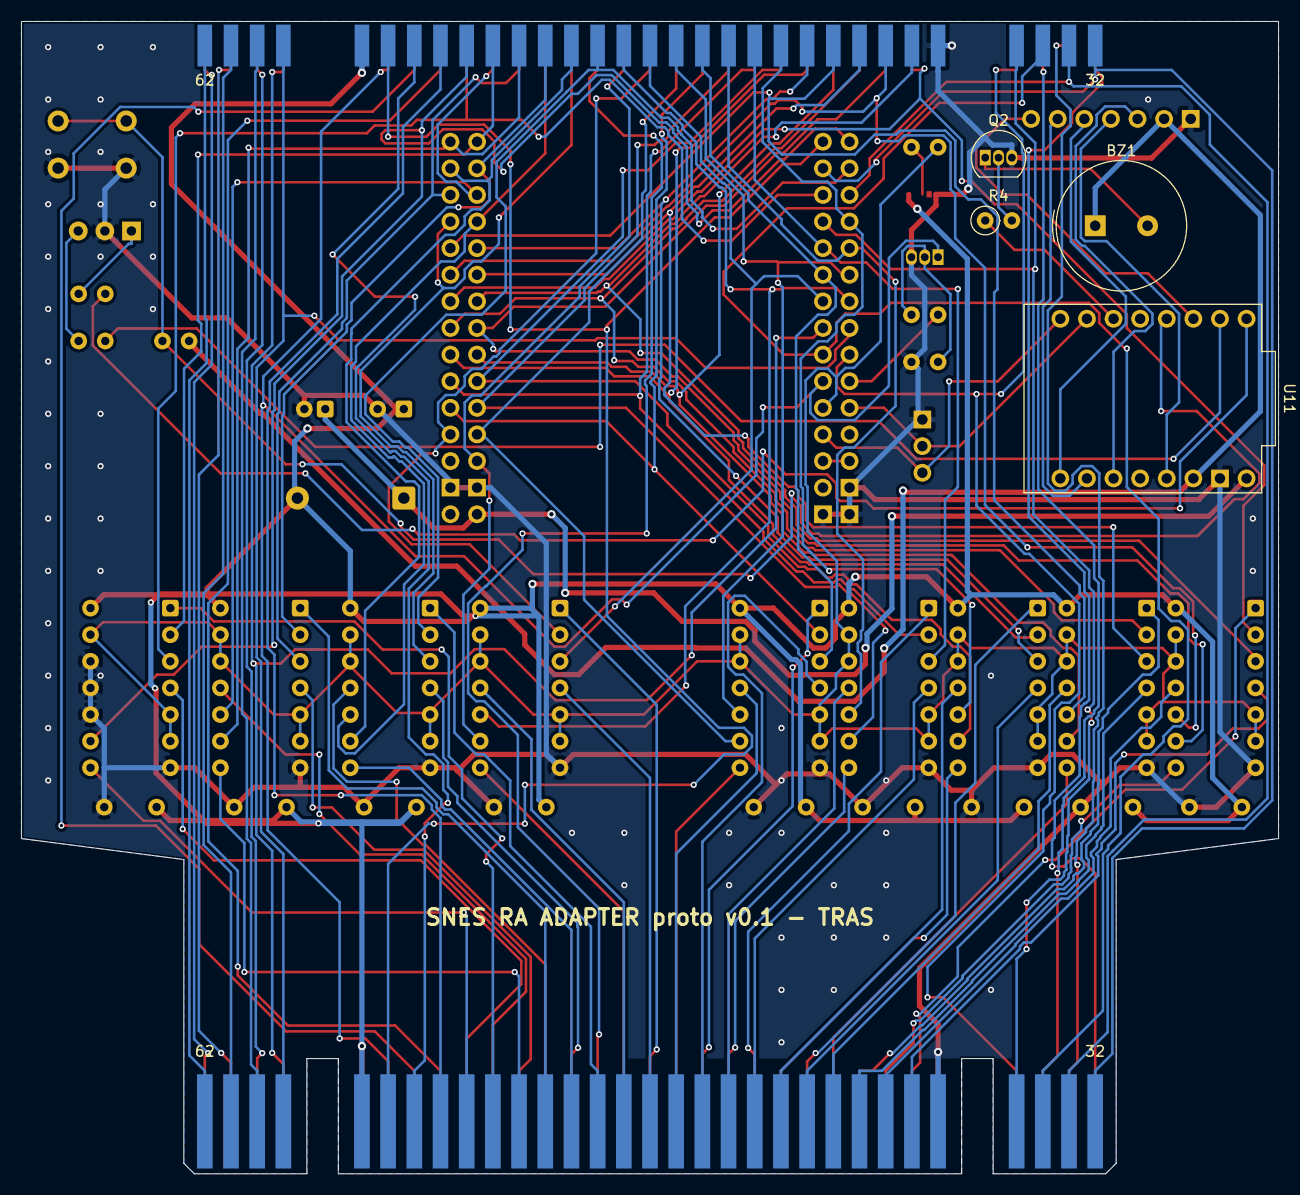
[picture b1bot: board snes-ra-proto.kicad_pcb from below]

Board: 2 copper layers, 120.0 x 110.0 mm, 40 parts (4 on the bottom side), 116 nets.
